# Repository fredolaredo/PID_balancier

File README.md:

# PID_balancier

test de mise en oeuvre de PID sur un balancier

## objectif

placer la boule au milieu du balancier en controlant la vitesse du moteur par PID

## composants

limiteur de tension L7805 (5V)

atmega328 en 5V / 16 Mhz (package DIP28)

TMC2208 : driver de moteur BL silencieux 

moteur NEMA17 classique

capteur de distance sharp 2Y1A02

## alimentation

entre 9v et 12v pour driver et uC

## modelisation 3D

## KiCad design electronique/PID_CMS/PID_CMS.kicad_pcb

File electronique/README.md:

fichiers au format kicad

PID : fichiers qui ont servi a faire le premier proto

PID_CMS : tentative de gravure de PCB avec composants de surface (en cours)

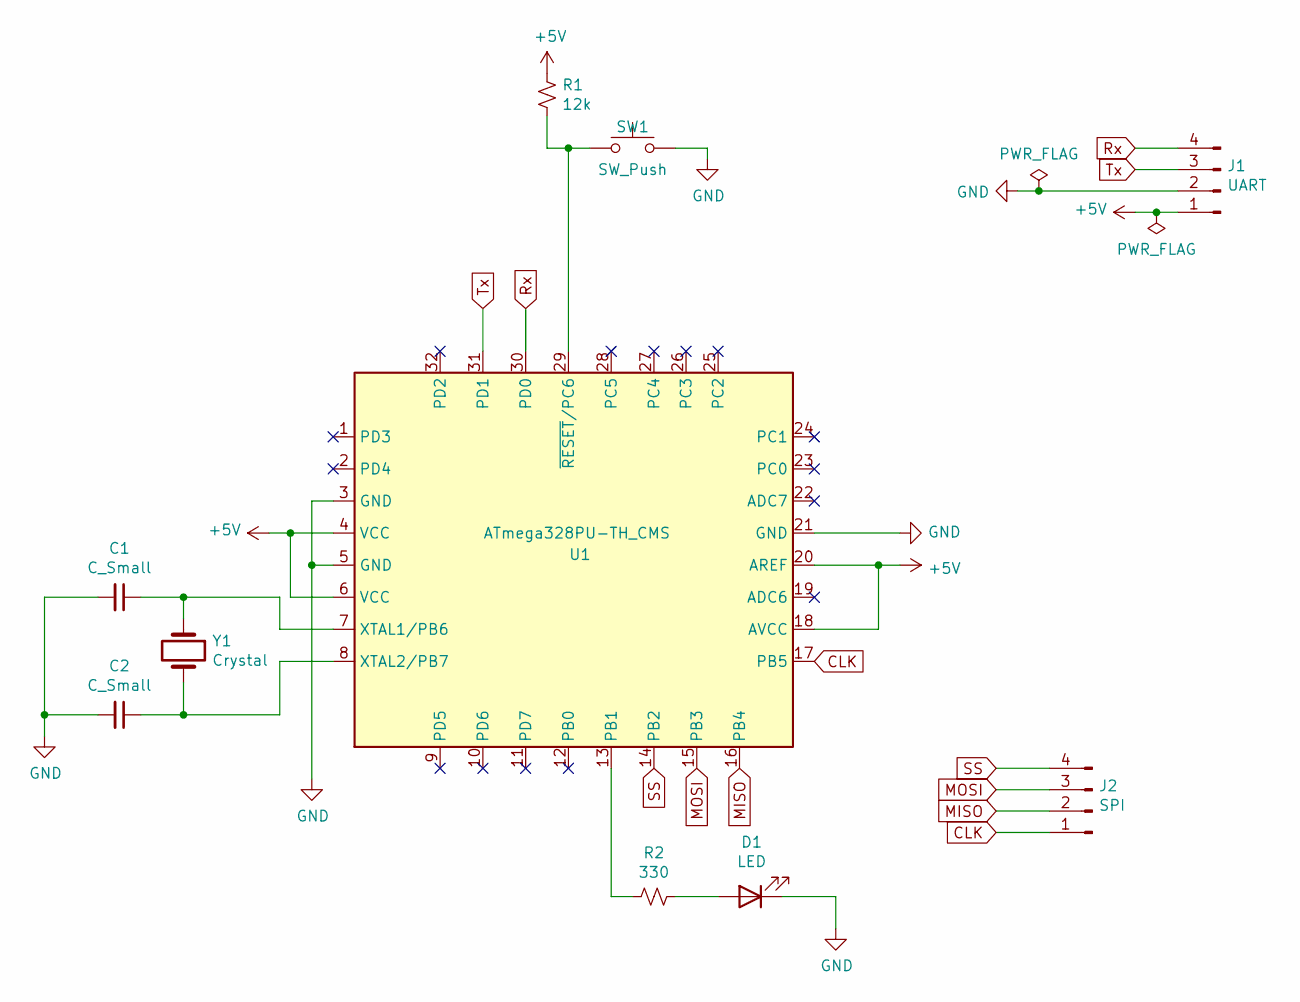
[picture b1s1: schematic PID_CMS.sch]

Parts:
C1, C2: C_Small; C_Disc_D4.3mm_W1.9mm_P5.00mm
D1: LED; LED_0805_2012Metric
J1: UART; PinHeader_1x04_P2.54mm_Horizontal
J2: SPI; PinHeader_1x04_P2.54mm_Horizontal
R1: 12k; R_1206_3216Metric
R2: 330; R_1206_3216Metric
SW1: SW_Push; SW_Push_SPST_NO_Alps_SKRK
U1: ATmega328PU-TH_CMS; TQFP-32_7x7mm_P0.8mm
Y1: Crystal; Resonator-2Pin_W10.0mm_H5.0mm

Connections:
+5V: J1.1, R1.1, U1.4 (VCC), U1.6 (VCC), U1.18 (AVCC), U1.20 (AREF)
CLK: J2.1, U1.17 (PB5)
GND: C1.2, C2.2, D1.1 (K), J1.2, SW1.2, U1.3 (GND), U1.5 (GND), U1.21 (GND)
MISO: J2.2, U1.16 (PB4)
MOSI: J2.3, U1.15 (PB3)
unnamed: C1.1, U1.7 (XTAL1/PB6), Y1.1
unnamed: C2.1, U1.8 (XTAL2/PB7), Y1.2
unnamed: D1.2 (A), R2.1
unnamed: R1.2, SW1.1, U1.29 (~RESET~/PC6)
unnamed: R2.2, U1.13 (PB1)
Rx: J1.4, U1.30 (PD0)
SS: J2.4, U1.14 (PB2)
Tx: J1.3, U1.31 (PD1)

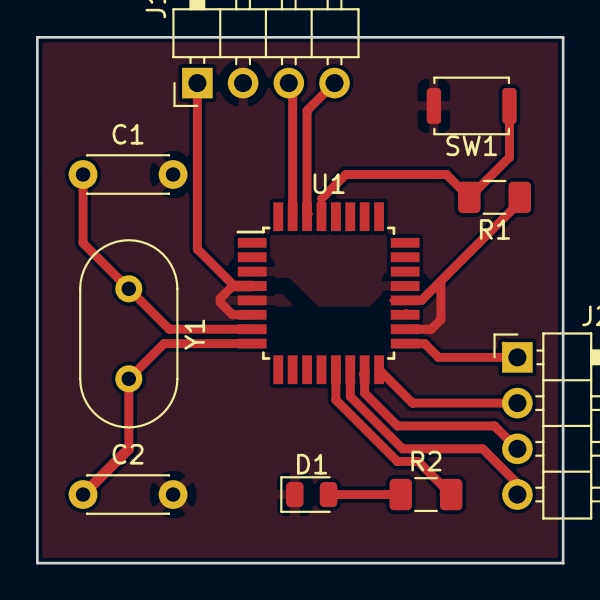
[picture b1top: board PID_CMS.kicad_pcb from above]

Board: 2 copper layers, 29.2 x 29.2 mm, 10 parts (0 on the bottom side), 13 nets.

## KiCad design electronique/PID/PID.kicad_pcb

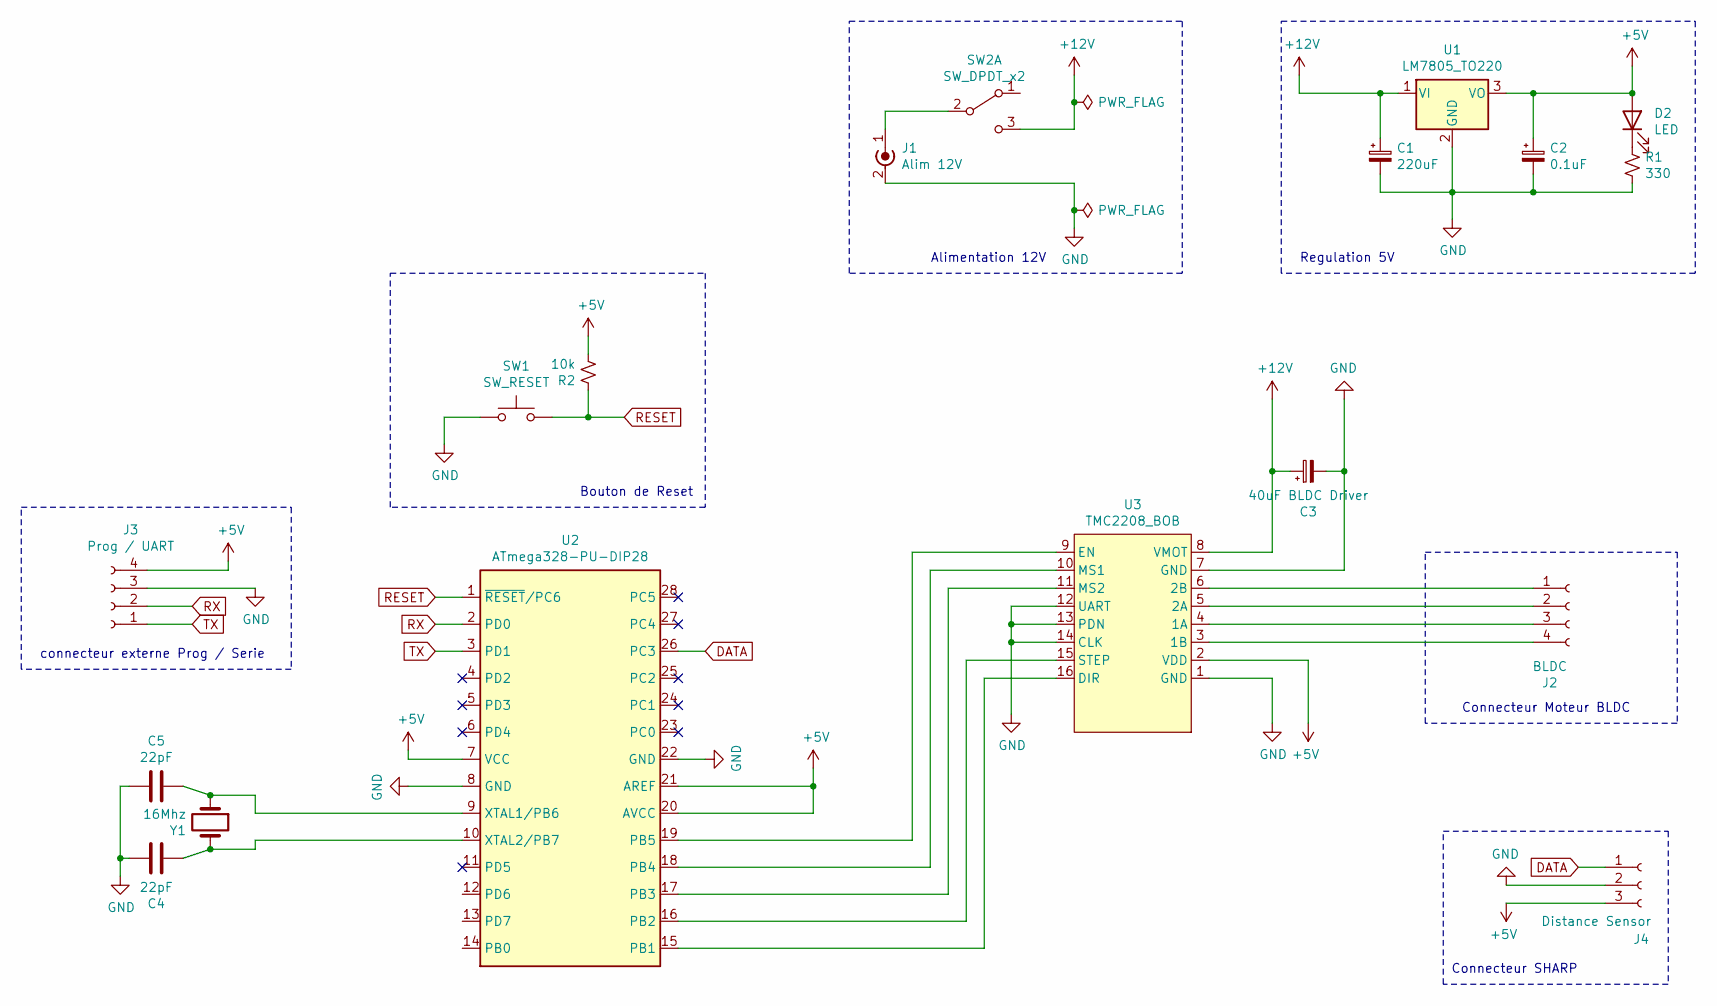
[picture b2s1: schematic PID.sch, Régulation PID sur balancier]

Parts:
C1: 220uF; CP_Radial_D5.0mm_P2.50mm
C2: 0.1uF; CP_Radial_D5.0mm_P2.50mm
C3: 40uF BLDC Driver; CP_Radial_D8.0mm_P3.50mm
C4, C5: 22pF; C_Disc_D3.0mm_W1.6mm_P2.50mm
D2: LED; LED_D5.0mm
J1: Alim 12V; BarrelJack_Horizontal
J2: BLDC; PinHeader_1x04_P2.54mm_Vertical
J3: Prog / UART; PinHeader_1x04_P2.54mm_Vertical
J4: Distance Sensor; PinHeader_1x03_P2.54mm_Vertical
R1: 330; R_Axial_DIN0204_L3.6mm_D1.6mm_P7.62mm_Horizontal
R2: 10k; R_Axial_DIN0204_L3.6mm_D1.6mm_P7.62mm_Horizontal
SW1: SW_RESET; SW_PUSH_6mm
SW2: SW_DPDT_x2; PinHeader_1x03_P2.54mm_Vertical
U1: LM7805_TO220; TO-220-3_Vertical
U2: ATmega328-PU-DIP28; DIP-28_W7.62mm
U3: TMC2208_BOB
Y1: 16Mhz; Resonator-2Pin_W8.0mm_H3.5mm

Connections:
+5V: C2.1, D2.2 (A), J3.4, J4.3, R2.2, U1.3 (VO), U2.7 (VCC), U2.20 (AVCC), U2.21 (AREF), U3.2 (VDD)
+12V: C1.1, C3.1, SW2.3 (C), U1.1 (VI), U3.8 (VMOT)
DATA: J4.1, U2.26 (PC3)
GND: C1.2, C2.2, C3.2, C4.1, C5.2, J1.2 (Ext), J3.3, J4.2, R1.2, SW1.1, U1.2 (GND), U2.8 (GND), U2.22 (GND), U3.1 (GND), U3.7 (GND), U3.12 (UART), U3.13 (PDN), U3.14 (CLK)
unnamed: C4.2, U2.10 (XTAL2/PB7), Y1.2
unnamed: C5.1, U2.9 (XTAL1/PB6), Y1.1
unnamed: D2.1 (K), R1.1
unnamed: J1.1 (In), SW2.2 (B)
unnamed: J2.1, U3.6 (2B)
unnamed: J2.2, U3.5 (2A)
unnamed: J2.3, U3.4 (1A)
unnamed: J2.4, U3.3 (1B)
unnamed: U2.15 (PB1), U3.16 (DIR)
unnamed: U2.16 (PB2), U3.15 (STEP)
unnamed: U2.17 (PB3), U3.11 (MS2)
unnamed: U2.18 (PB4), U3.10 (MS1)
unnamed: U2.19 (PB5), U3.9 (EN)
RESET: R2.1, SW1.2, U2.1 (~RESET~/PC6)
RX: J3.2, U2.2 (PD0)
TX: J3.1, U2.3 (PD1)

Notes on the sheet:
connecteur externe Prog / Serie
Alimentation 12V
Connecteur Moteur BLDC
Regulation 5V
Bouton de Reset
Connecteur SHARP

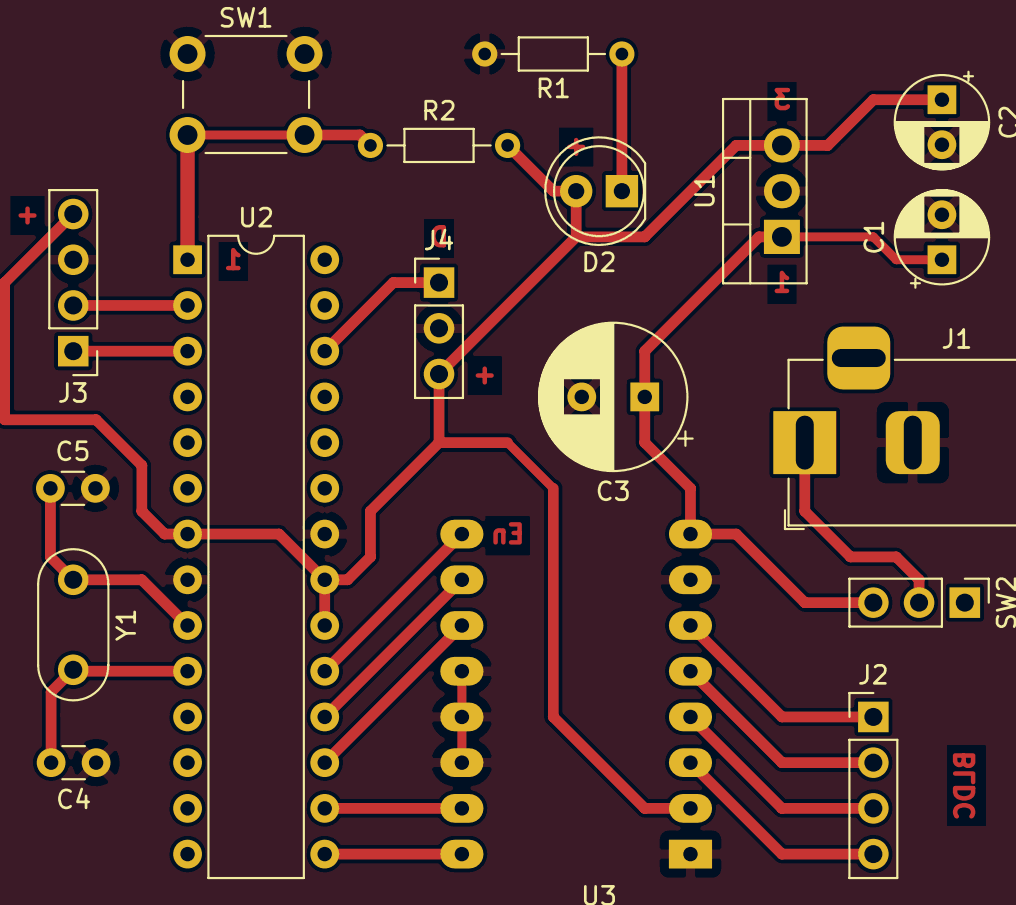
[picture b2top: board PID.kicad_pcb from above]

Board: 2 copper layers, 18 parts (0 on the bottom side), 20 nets.
